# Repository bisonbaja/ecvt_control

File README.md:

# eCVT Control for Bison Baja
eCVT Control System

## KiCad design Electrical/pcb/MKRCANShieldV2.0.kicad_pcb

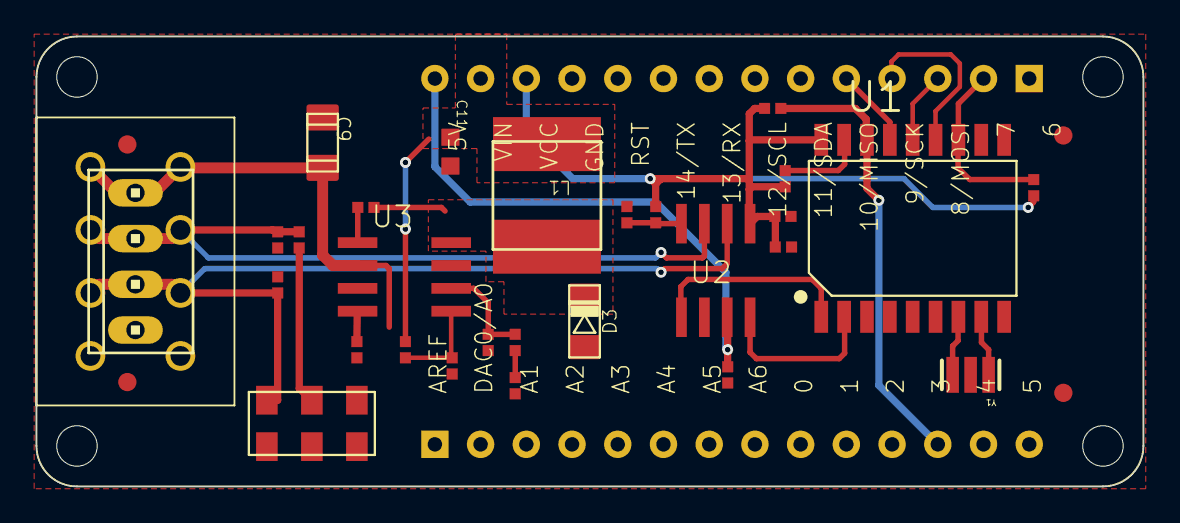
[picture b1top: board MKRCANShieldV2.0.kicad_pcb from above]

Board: 2 copper layers, 61.5 x 25.0 mm, 39 parts (0 on the bottom side), 25 nets.

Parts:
@HOLE0, @HOLE1, @HOLE2, @HOLE3: (no value)
C3, C4, C5, C10: 100n; 0402-1005X55N
C6: 8n2; 0402-1005X55N
C7: 4n7; 0402-1005X55N
C8: 110p; 0402-1005X55N
C9: 10uF; C1206
C11: 10u; 0603-1608X90N
D1, D2: PESD0402; 0402-1005X55N
D3: SS24FL; SOD123F
FRAME1: DNP; FRAME
L1: 15uH; SRN6045
MKR1: -; MKRBOARD-NH
R1, R2, R7, R9, R11: 10k2; 0402-1005X55N
R3: 120R; 0402-1005X55N
R4: 12k7; 0402-1005X55N
R8: 0R; 0402-1005X55N
R10: 1k91; 0402-1005X55N
SW1: -; CL-SB-22A
U1: MCP2515; SOIC18
U2: TJA1049T/3; SO08
U3: TPS54232DR; SO08
U$1, U$4, U$6, U$13: DNP; FD-1-1.5
X2: DNP; SPTAF1_4-3.5-IL
X3: -; MODULINO-4
Y1: 16MHz; RESONATOR

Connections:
+3V3: C3.1, C4.1, MKR1.VCC, R1.2, R2.2, R7.2, R11.2, U1.18, U2.5
+5V: C5.1, MKR1.5V, U2.3
CANH: D2.2, R3.1, U2.7, X2.3A, X2.3B, X3.3
CANL: D1.2, SW1.P$4, U2.6, X2.2A, X2.2B, X3.2
GND: C3.2, C4.2, C5.2, C6.2, C7.2, C8.2, C9.2, C11.2, D1.1, D2.1, D3.A, MKR1.GND, R8.1, R10.1, U1.9, U2.2, U3.7, X2.1A, X2.1B, X3.1, Y1.2
INT: MKR1.7, R7.1, U1.12
MISO: MKR1.10, U1.15
MOSI: MKR1.8, U1.14
unnamed: R3.2, SW1.P$5
unnamed: C7.1, R4.1
unnamed: R1.1, R8.2, U2.8
unnamed: C8.1, R4.2, U3.6
unnamed: C6.1, U3.4
unnamed: C9.1, U3.2, X2.4A, X2.4B, X3.4
unnamed: C10.1, U3.1
unnamed: C10.2, D3.C, L1.1, U3.8
unnamed: R9.1, R10.2, U3.5
unnamed: MKR1.3, R11.1, U1.16
unnamed: U1.7, Y1.3
unnamed: U1.8, Y1.1
RST_N: R2.1, U1.17
RX_CAN: U1.2, U2.4
SCK: MKR1.9, U1.13
TX_CAN: U1.1, U2.1
VIN: C11.1, L1.2, MKR1.VIN, R9.2

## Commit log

2024-11-08 added electrical
2024-11-12 name
2024-11-21 djdfj
2025-01-28 basically all of main
2025-01-28 changed name and moved files
2025-01-28 Updated name in more places
2025-01-29 documentation
2025-01-31 Added more ready/error signaling during startup, and removed the feed-forward element.
2025-02-04 new belt model
2025-02-04 1322132154
2025-02-06 mo changes
2025-02-06 fixed text formatting
2025-02-06 num mags
2025-02-06 restructured
2025-02-07 some new matlab sims
2025-02-11 commit before refactor PID
2025-02-12 separate averaging from magnet count, tweaked PID parameters in prelim testing
2025-02-13 PID changes
2025-02-19 Minor changes, incl. to max speed and accel of stepper
2025-02-27 create branch for esp32
2025-02-28 bluetooth
2025-03-01 more changes
2025-03-02 serial command processing and accelerometer
2025-03-03 Serial parameter updates
2025-03-04 split up program
2025-03-04 FIxing stuff in-progress, this does not work right now.
2025-03-04 okay it builds now
2025-03-05 Simplified the code significantly
2025-03-06 improved logging system
2025-03-06 Ported to MKRZero
2025-03-11 debugging
2025-04-04 minor changes to formatting
2025-04-14 lots of test runs and minor changes
2025-04-22 new logs
2025-04-22 lil change to config
2025-04-30 Minor changes

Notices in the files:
parts and their libraries:
This file is licensed under : CC-SA-BY-NC
